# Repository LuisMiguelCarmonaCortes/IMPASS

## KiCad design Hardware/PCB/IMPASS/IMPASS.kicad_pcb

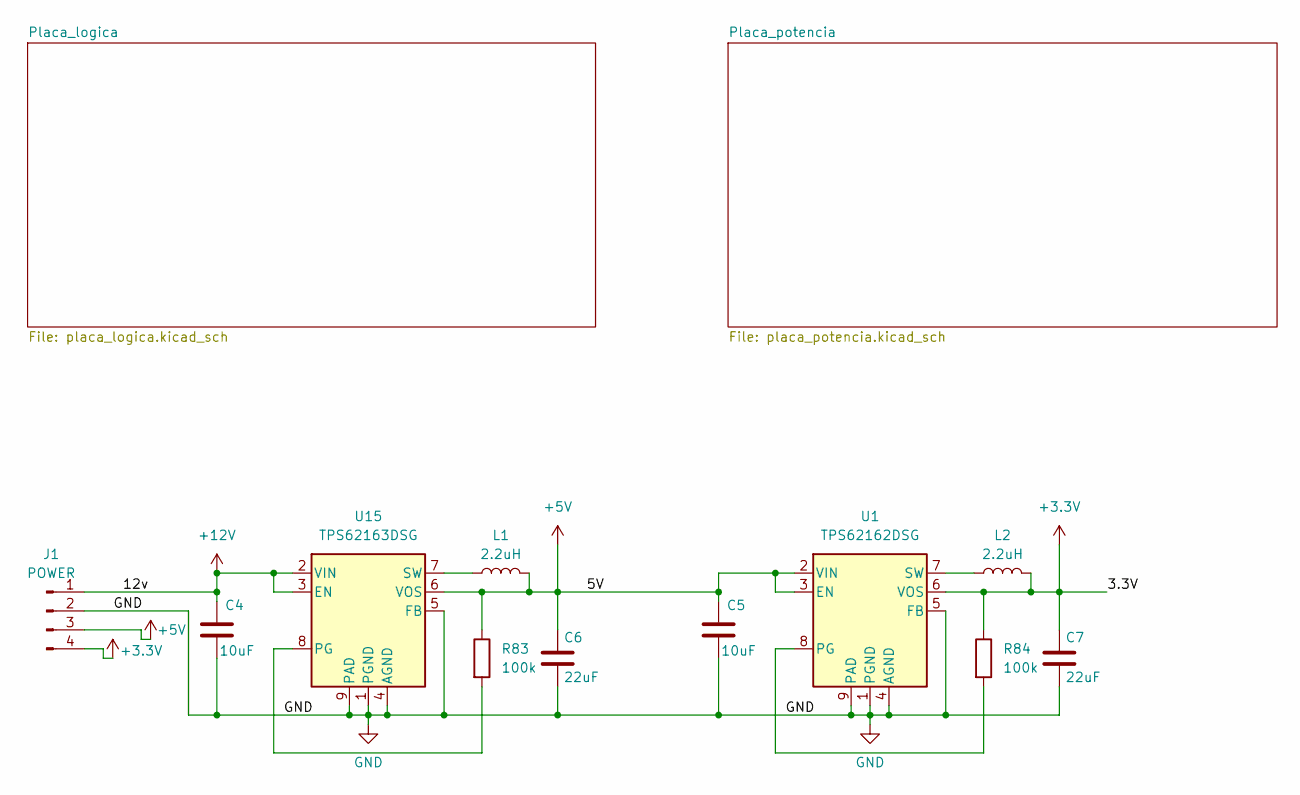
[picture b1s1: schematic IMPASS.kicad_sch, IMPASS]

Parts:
C4, C5: 10uF; C_0805_2012Metric
C6, C7: 22uF; C_0603_1608Metric
J1: POWER; PinHeader_1x04_P2.54mm_Vertical
L1, L2: 2.2uH; L_0603_1608Metric
R83, R84: 100k; R_0603_1608Metric
U1: TPS62162DSG; WSON-8-1EP_2x2mm_P0.5mm_EP0.9x1.6mm_ThermalVias
U15: TPS62163DSG; WSON-8-1EP_2x2mm_P0.5mm_EP0.9x1.6mm_ThermalVias

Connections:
+3.3V: C7.1, J1.4, L2.2, R84.1, U1.6 (VOS); also elsewhere on the board
+5V: C5.1, C6.1, J1.3, L1.2, R83.1, U1.2 (VIN), U1.3 (EN), U15.6 (VOS); also elsewhere on the board
+12V: C4.1, J1.1, U15.2 (VIN), U15.3 (EN); also elsewhere on the board
GND: C4.2, C5.2, C6.2, C7.2, J1.2, U1.1 (PGND), U1.4 (AGND), U1.5 (FB), U1.9 (PAD), U15.1 (PGND), U15.4 (AGND), U15.5 (FB), U15.9 (PAD); also elsewhere on the board
unnamed: R84.2, U1.8 (PG)
unnamed: L2.1, U1.7 (SW)
unnamed: R83.2, U15.8 (PG)
unnamed: L1.1, U15.7 (SW)

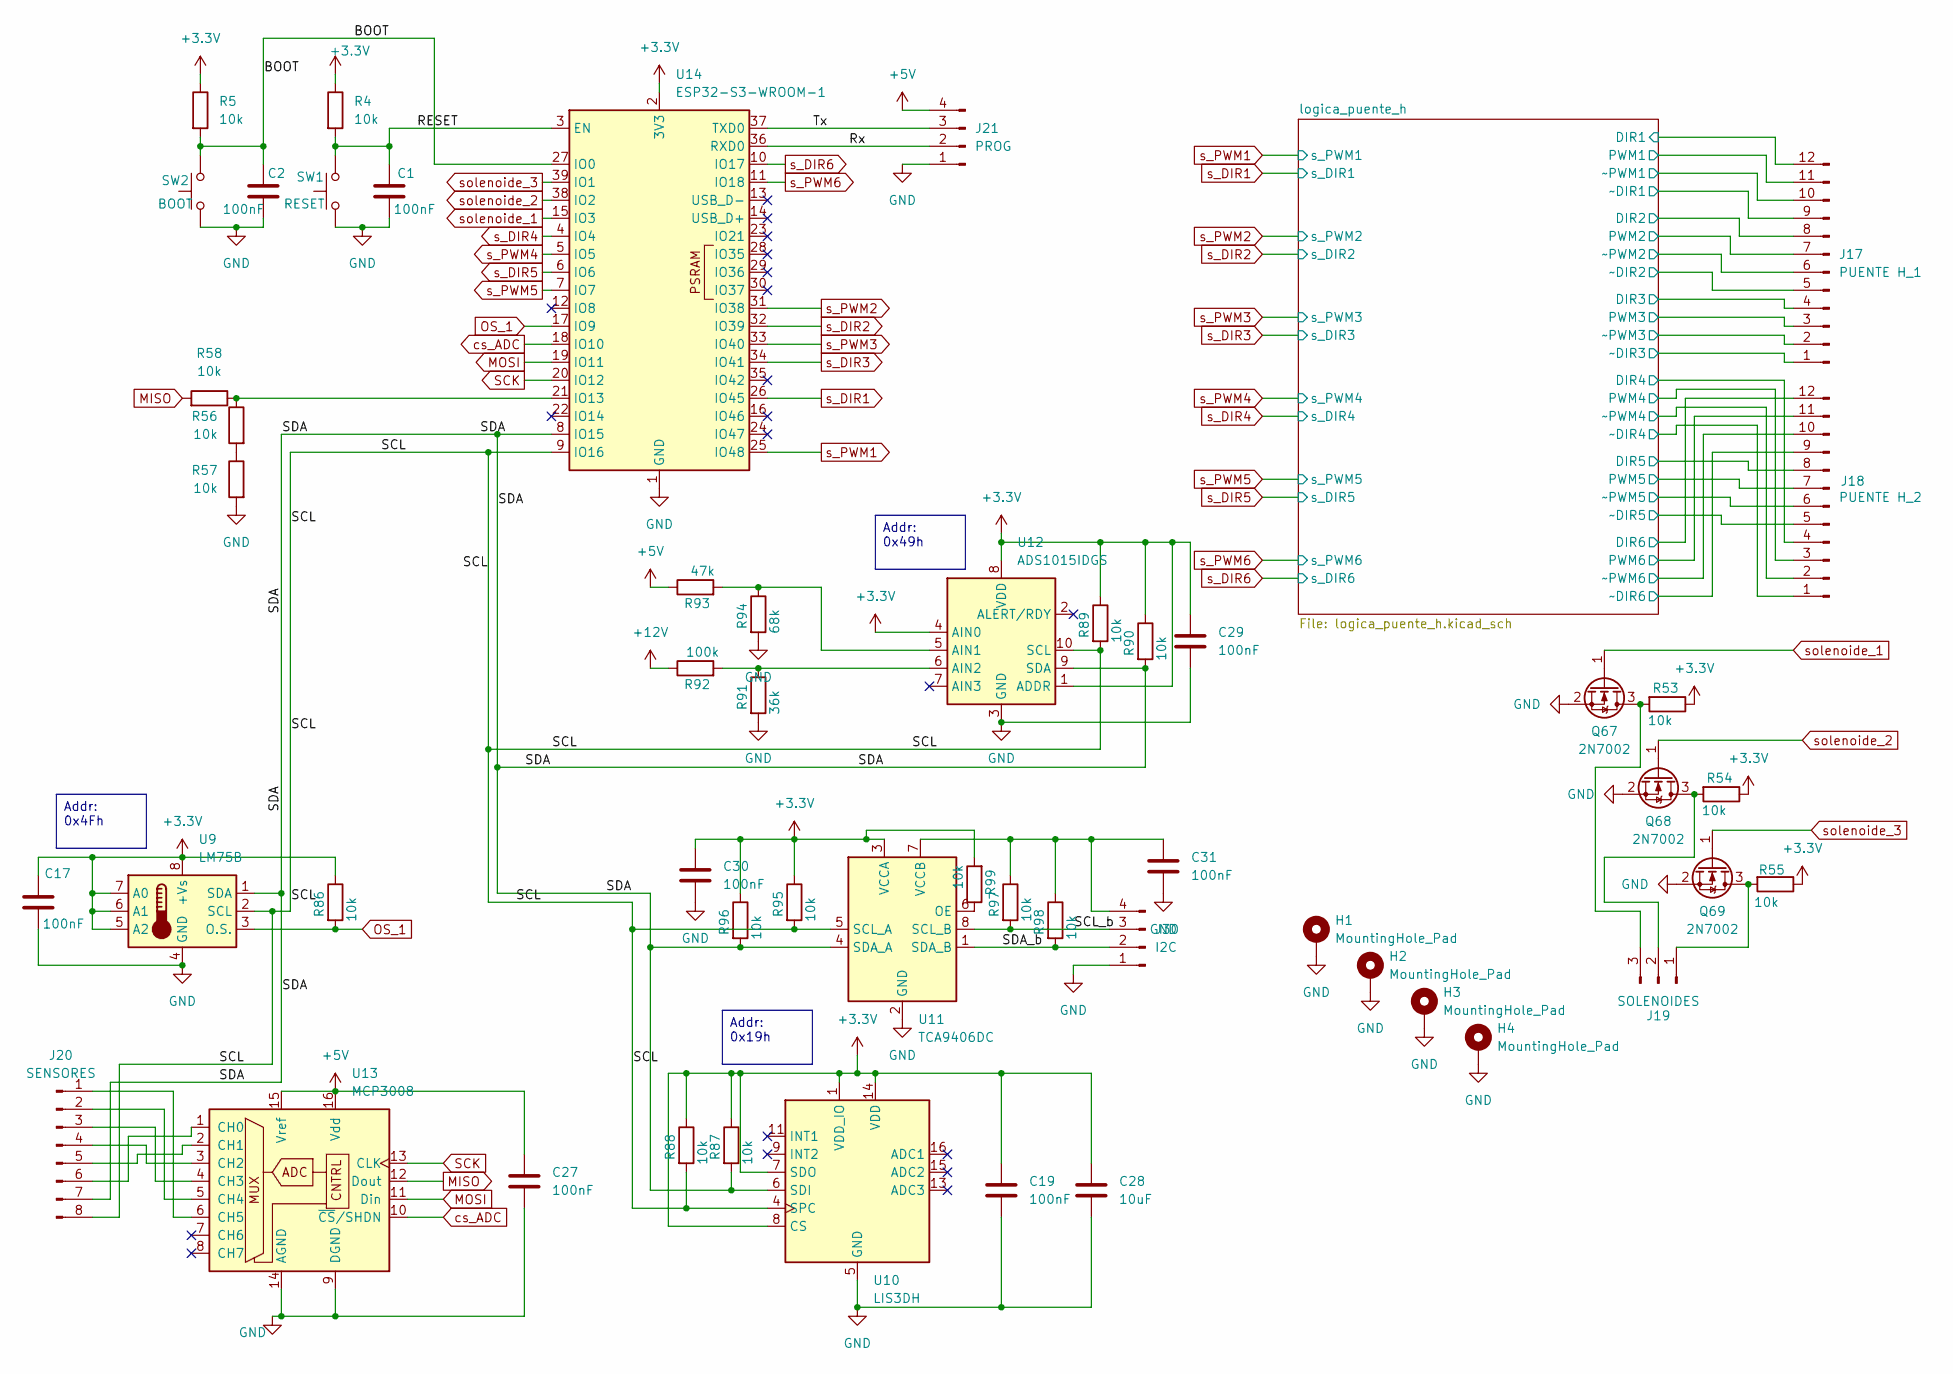
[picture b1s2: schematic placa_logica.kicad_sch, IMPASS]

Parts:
C1, C2, C17, C19, C27, C29, C30, C31: 100nF; C_0603_1608Metric
C28: 10uF; C_0603_1608Metric
H1, H2, H3, H4: MountingHole_Pad; MountingHole_2.2mm_M2_DIN965_Pad
J17: PUENTE H_1; PinHeader_1x12_P2.54mm_Vertical
J18: PUENTE H_2; PinHeader_1x12_P2.54mm_Vertical
J19: SOLENOIDES; PinHeader_1x03_P2.54mm_Vertical
J20: SENSORES; PinHeader_1x08_P2.54mm_Vertical
J21: PROG; PinHeader_1x04_P2.54mm_Horizontal
J30: I2C; PinHeader_1x04_P2.54mm_Horizontal
Q67, Q68, Q69: 2N7002; SOT-23
R4, R5, R53, R54, R55, R56, R57, R58, R86, R87, R88, R89, R90, R95, R96, R97, R98, R99: 10k; R_0603_1608Metric
R91: 36k; R_0603_1608Metric
R92: 100k; R_0603_1608Metric
R93: 47k; R_0603_1608Metric
R94: 68k; R_0603_1608Metric
SW1: RESET; SW_PUSH_6mm_H5mm
SW2: BOOT; SW_PUSH_6mm_H5mm
U9: LM75B; SOIC-8_3.9x4.9mm_P1.27mm
U10: LIS3DH; LGA-16_3x3mm_P0.5mm_LayoutBorder3x5y
U11: TCA9406DC; SSOP-8_2.95x2.8mm_P0.65mm
U12: ADS1015IDGS; TSSOP-10_3x3mm_P0.5mm
U13: MCP3008; SOIC-16_3.9x9.9mm_P1.27mm
U14: ESP32-S3-WROOM-1

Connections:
+3.3V: C17.1, C19.1, C28.1, C29.1, C30.1, R4.1, R5.1, R53.1, R54.1, R55.1, R86.1, R87.1, R88.1, R89.1, R90.1, R95.1, R96.1, R99.2, U9.5 (A2), U9.6 (A1), U9.7 (A0), U9.8 (+Vs), U10.1 (VDD_IO), U10.7 (SDO), U10.8 (CS), U10.14 (VDD), U11.3 (VCCA), U12.1 (ADDR), U12.4 (AIN0), U12.8 (VDD), U14.2 (3V3); also elsewhere on the board
+5V: C27.1, J21.4, R93.1, U13.15 (Vref), U13.16 (Vdd); also elsewhere on the board
+12V: R92.1; also elsewhere on the board
/Placa_logica/BOOT: C2.1, R5.2, SW2.2, U14.27 (IO0)
/Placa_logica/RESET: C1.1, R4.2, SW1.2, U14.3 (EN)
/Placa_logica/Rx: J21.2, U14.36 (RXD0)
/Placa_logica/SCL: J20.8, R88.2, R89.2, R95.2, U9.2 (SCL), U10.4 (SPC), U11.5 (SCL_A), U12.10 (SCL), U14.9 (IO16)
/Placa_logica/SCL_b: J30.3, R97.2, U11.8 (SCL_B)
/Placa_logica/SDA: J20.7, R87.2, R90.2, R96.2, U9.1 (SDA), U10.6 (SDI), U11.4 (SDA_A), U12.9 (SDA), U14.8 (IO15)
/Placa_logica/SDA_b: J30.2, R98.2, U11.1 (SDA_B)
/Placa_logica/Tx: J21.3, U14.37 (TXD0)
/Placa_logica/logica_puente_h/PWM1: J17.11; also elsewhere on the board
/Placa_logica/logica_puente_h/PWM2: J17.7; also elsewhere on the board
/Placa_logica/logica_puente_h/PWM3: J17.3; also elsewhere on the board
/Placa_logica/logica_puente_h/PWM4: J18.3; also elsewhere on the board
/Placa_logica/logica_puente_h/PWM5: J18.7; also elsewhere on the board
/Placa_logica/logica_puente_h/PWM6: J18.11; also elsewhere on the board
/Placa_logica/logica_puente_h/~DIR1: J17.9; also elsewhere on the board
/Placa_logica/logica_puente_h/~DIR2: J17.5; also elsewhere on the board
/Placa_logica/logica_puente_h/~DIR3: J17.1; also elsewhere on the board
/Placa_logica/logica_puente_h/~DIR4: J18.1; also elsewhere on the board
/Placa_logica/logica_puente_h/~DIR5: J18.5; also elsewhere on the board
/Placa_logica/logica_puente_h/~DIR6: J18.9; also elsewhere on the board
/Placa_logica/logica_puente_h/~PWM1: J17.10; also elsewhere on the board
/Placa_logica/logica_puente_h/~PWM2: J17.6; also elsewhere on the board
/Placa_logica/logica_puente_h/~PWM3: J17.2; also elsewhere on the board
/Placa_logica/logica_puente_h/~PWM4: J18.2; also elsewhere on the board
/Placa_logica/logica_puente_h/~PWM5: J18.6; also elsewhere on the board
/Placa_logica/logica_puente_h/~PWM6: J18.10; also elsewhere on the board
GND: C1.2, C2.2, C17.2, C19.2, C27.2, C28.2, C29.2, C30.2, C31.2, H1.1 (1_1), H2.1 (1_1), H3.1 (1_1), H4.1 (1_1), J21.1, J30.1, Q67.2 (S), Q68.2 (S), Q69.2 (S), R57.2, R91.2, R94.2, SW1.1, SW2.1, U9.4 (GND), U10.5 (GND), U10.10 (GND), U10.12 (GND), U11.2 (GND), U12.3 (GND), U13.9 (DGND), U13.14 (AGND), U14.1 (GND), U14.40 (GND), U14.41 (GND); also elsewhere on the board
MISO: R58.2, U13.12 (Dout)
MOSI: U13.11 (Din), U14.19 (IO11)
unnamed: J19.1, Q69.3 (D), R55.2
unnamed: J19.2, Q68.3 (D), R54.2
unnamed: J19.3, Q67.3 (D), R53.2
unnamed: J20.1, U13.6 (CH5)
unnamed: J20.2, U13.5 (CH4)
unnamed: J20.3, U13.4 (CH3)
unnamed: J20.4, U13.3 (CH2)
unnamed: J20.5, U13.2 (CH1)
unnamed: J20.6, U13.1 (CH0)
unnamed: C31.1, J30.4, R97.1, R98.1, U11.7 (VCCB)
unnamed: R56.2, R57.1
unnamed: R99.1, U11.6 (OE)
unnamed: R93.2, R94.1, U12.5 (AIN1)
unnamed: R91.1, R92.2, U12.6 (AIN2)
unnamed: R56.1, R58.1, U14.21 (IO13)
OS_1: R86.2, U9.3 (O.S.), U14.17 (IO9)
SCK: U13.13 (CLK), U14.20 (IO12)
cs_ADC: U13.10 (~CS/SHDN), U14.18 (IO10)
s_DIR1: J17.12, U14.26 (IO45); also elsewhere on the board
s_DIR2: J17.8, U14.32 (IO39); also elsewhere on the board
s_DIR3: J17.4, U14.34 (IO41); also elsewhere on the board
s_DIR4: J18.4, U14.4 (IO4); also elsewhere on the board
s_DIR5: J18.8, U14.6 (IO6); also elsewhere on the board
s_DIR6: J18.12, U14.10 (IO17); also elsewhere on the board
s_PWM1: U14.25 (IO48); also elsewhere on the board
s_PWM2: U14.31 (IO38); also elsewhere on the board
s_PWM3: U14.33 (IO40); also elsewhere on the board
s_PWM4: U14.5 (IO5); also elsewhere on the board
s_PWM5: U14.7 (IO7); also elsewhere on the board
s_PWM6: U14.11 (IO18); also elsewhere on the board
solenoide_1: Q67.1 (G), U14.15 (IO3)
solenoide_2: Q68.1 (G), U14.38 (IO2)
solenoide_3: Q69.1 (G), U14.39 (IO1)

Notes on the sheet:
Addr: 0x4Fh
Addr: 0x19h
Addr: 0x49h

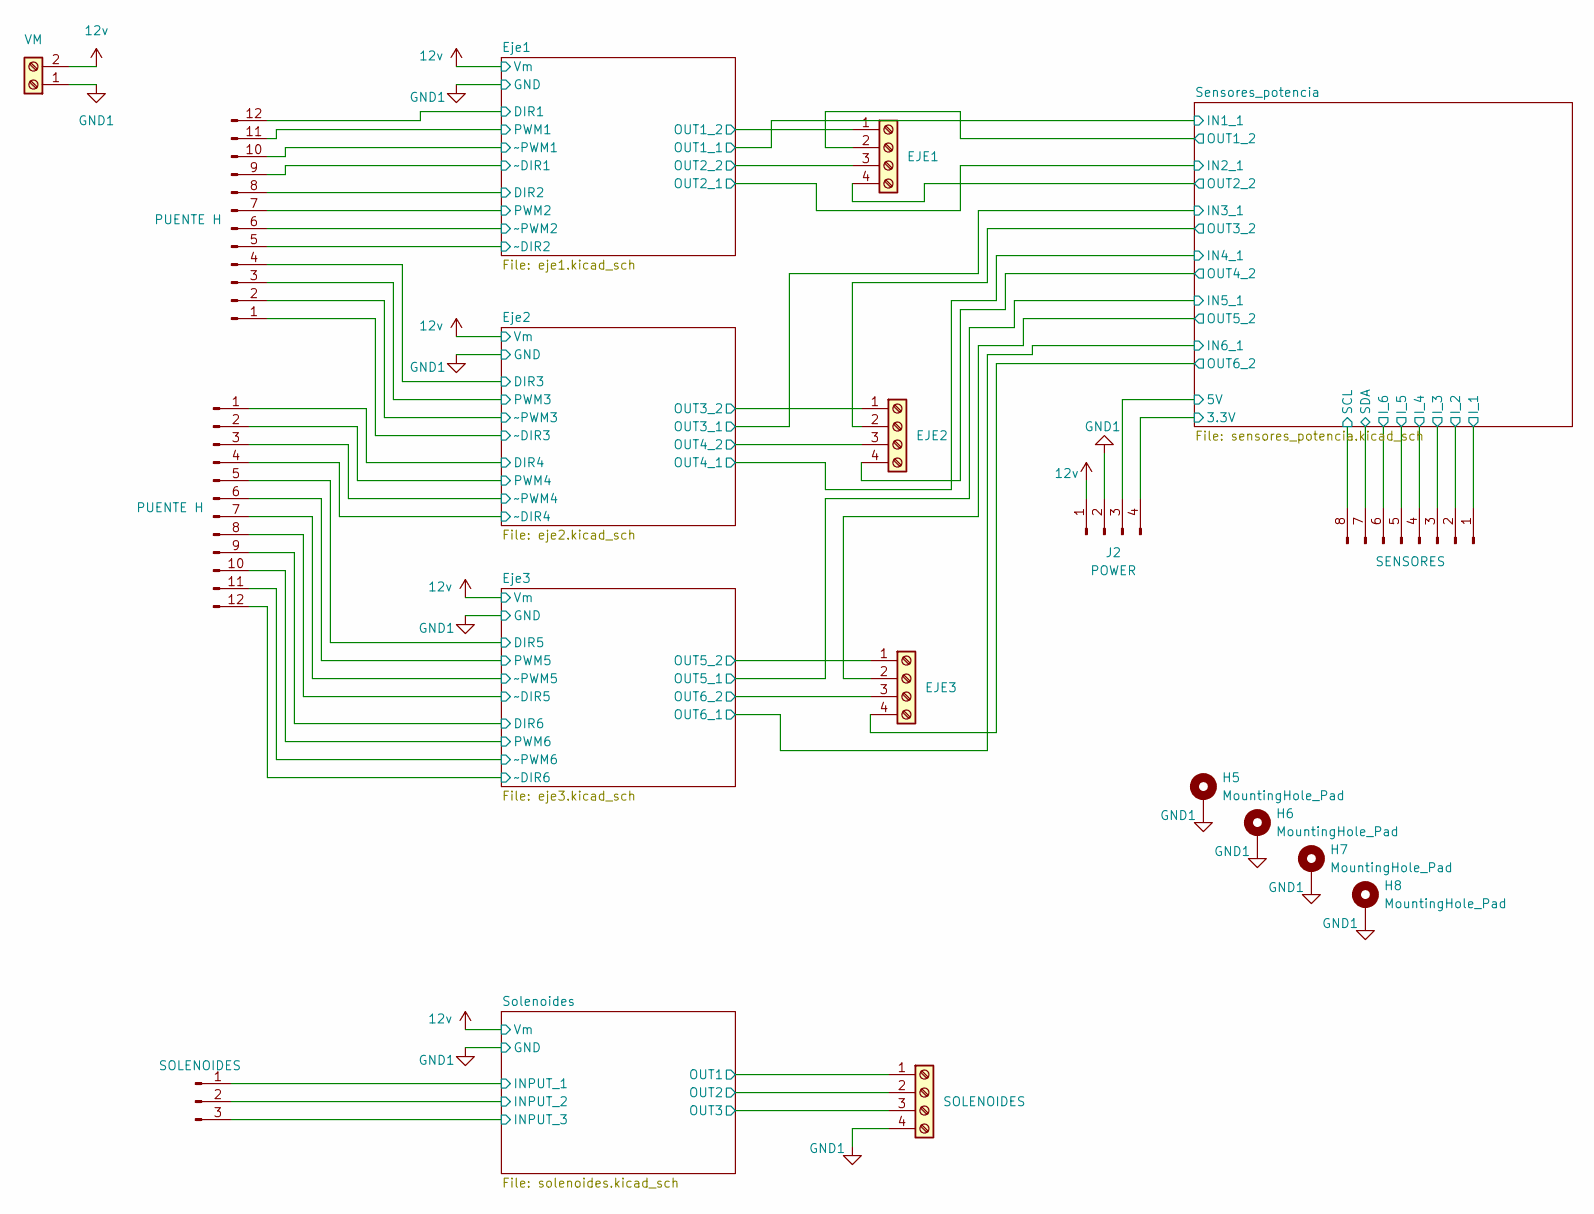
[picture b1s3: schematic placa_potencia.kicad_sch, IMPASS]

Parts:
H5, H6, H7, H8: MountingHole_Pad; MountingHole_2.2mm_M2_DIN965_Pad
J2: POWER; PinHeader_1x04_P2.54mm_Vertical
J11: SOLENOIDES; PinHeader_1x03_P2.54mm_Vertical
J22: VM; TerminalBlock_Phoenix_PT-1,5-2-3.5-H_1x02_P3.50mm_Horizontal
J23: EJE1; TerminalBlock_Phoenix_PT-1,5-4-3.5-H_1x04_P3.50mm_Horizontal
J24: EJE2; TerminalBlock_Phoenix_PT-1,5-4-3.5-H_1x04_P3.50mm_Horizontal
J25: EJE3; TerminalBlock_Phoenix_PT-1,5-4-3.5-H_1x04_P3.50mm_Horizontal
J26: SOLENOIDES; TerminalBlock_Phoenix_PT-1,5-4-3.5-H_1x04_P3.50mm_Horizontal
J27, J28: PUENTE H; PinHeader_1x12_P2.54mm_Vertical
J29: SENSORES; PinHeader_1x08_P2.54mm_Vertical

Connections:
12v: J2.1, J22.2; also elsewhere on the board
/Placa_potencia/Eje1/DIR1: J28.12; also elsewhere on the board
/Placa_potencia/Eje1/DIR2: J28.8; also elsewhere on the board
/Placa_potencia/Eje1/OUT1_2: J23.1; also elsewhere on the board
/Placa_potencia/Eje1/OUT2_2: J23.3; also elsewhere on the board
/Placa_potencia/Eje1/PWM1: J28.11; also elsewhere on the board
/Placa_potencia/Eje1/PWM2: J28.7; also elsewhere on the board
/Placa_potencia/Eje1/~DIR1: J28.9; also elsewhere on the board
/Placa_potencia/Eje1/~DIR2: J28.5; also elsewhere on the board
/Placa_potencia/Eje1/~PWM1: J28.10; also elsewhere on the board
/Placa_potencia/Eje1/~PWM2: J28.6; also elsewhere on the board
/Placa_potencia/Eje2/DIR3: J28.4; also elsewhere on the board
/Placa_potencia/Eje2/DIR4: J27.1; also elsewhere on the board
/Placa_potencia/Eje2/OUT3_2: J24.1; also elsewhere on the board
/Placa_potencia/Eje2/OUT4_2: J24.3; also elsewhere on the board
/Placa_potencia/Eje2/PWM3: J28.3; also elsewhere on the board
/Placa_potencia/Eje2/PWM4: J27.2; also elsewhere on the board
/Placa_potencia/Eje2/~DIR3: J28.1; also elsewhere on the board
/Placa_potencia/Eje2/~DIR4: J27.4; also elsewhere on the board
/Placa_potencia/Eje2/~PWM3: J28.2; also elsewhere on the board
/Placa_potencia/Eje2/~PWM4: J27.3; also elsewhere on the board
/Placa_potencia/Eje3/DIR5: J27.5; also elsewhere on the board
/Placa_potencia/Eje3/DIR6: J27.9; also elsewhere on the board
/Placa_potencia/Eje3/OUT5_2: J25.1; also elsewhere on the board
/Placa_potencia/Eje3/OUT6_2: J25.3; also elsewhere on the board
/Placa_potencia/Eje3/PWM5: J27.6; also elsewhere on the board
/Placa_potencia/Eje3/PWM6: J27.10; also elsewhere on the board
/Placa_potencia/Eje3/~DIR5: J27.8; also elsewhere on the board
/Placa_potencia/Eje3/~DIR6: J27.12; also elsewhere on the board
/Placa_potencia/Eje3/~PWM5: J27.7; also elsewhere on the board
/Placa_potencia/Eje3/~PWM6: J27.11; also elsewhere on the board
/Placa_potencia/Sensores_potencia/3.3V: J2.4; also elsewhere on the board
/Placa_potencia/Sensores_potencia/5V: J2.3; also elsewhere on the board
/Placa_potencia/Sensores_potencia/I_1: J29.1; also elsewhere on the board
/Placa_potencia/Sensores_potencia/I_2: J29.2; also elsewhere on the board
/Placa_potencia/Sensores_potencia/I_3: J29.3; also elsewhere on the board
/Placa_potencia/Sensores_potencia/I_4: J29.4; also elsewhere on the board
/Placa_potencia/Sensores_potencia/I_5: J29.5; also elsewhere on the board
/Placa_potencia/Sensores_potencia/I_6: J29.6; also elsewhere on the board
/Placa_potencia/Sensores_potencia/OUT1_2: J23.2; also elsewhere on the board
/Placa_potencia/Sensores_potencia/OUT2_2: J23.4; also elsewhere on the board
/Placa_potencia/Sensores_potencia/OUT3_2: J24.2; also elsewhere on the board
/Placa_potencia/Sensores_potencia/OUT4_2: J24.4; also elsewhere on the board
/Placa_potencia/Sensores_potencia/OUT5_2: J25.2; also elsewhere on the board
/Placa_potencia/Sensores_potencia/OUT6_2: J25.4; also elsewhere on the board
/Placa_potencia/Sensores_potencia/SCL: J29.8; also elsewhere on the board
/Placa_potencia/Sensores_potencia/SDA: J29.7; also elsewhere on the board
/Placa_potencia/Solenoides/INPUT_1: J11.1; also elsewhere on the board
/Placa_potencia/Solenoides/INPUT_2: J11.2; also elsewhere on the board
/Placa_potencia/Solenoides/INPUT_3: J11.3; also elsewhere on the board
/Placa_potencia/Solenoides/OUT1: J26.1; also elsewhere on the board
/Placa_potencia/Solenoides/OUT2: J26.2; also elsewhere on the board
/Placa_potencia/Solenoides/OUT3: J26.3; also elsewhere on the board
GND1: H5.1 (1_1), H6.1 (1_1), H7.1 (1_1), H8.1 (1_1), J2.2, J22.1, J26.4; also elsewhere on the board

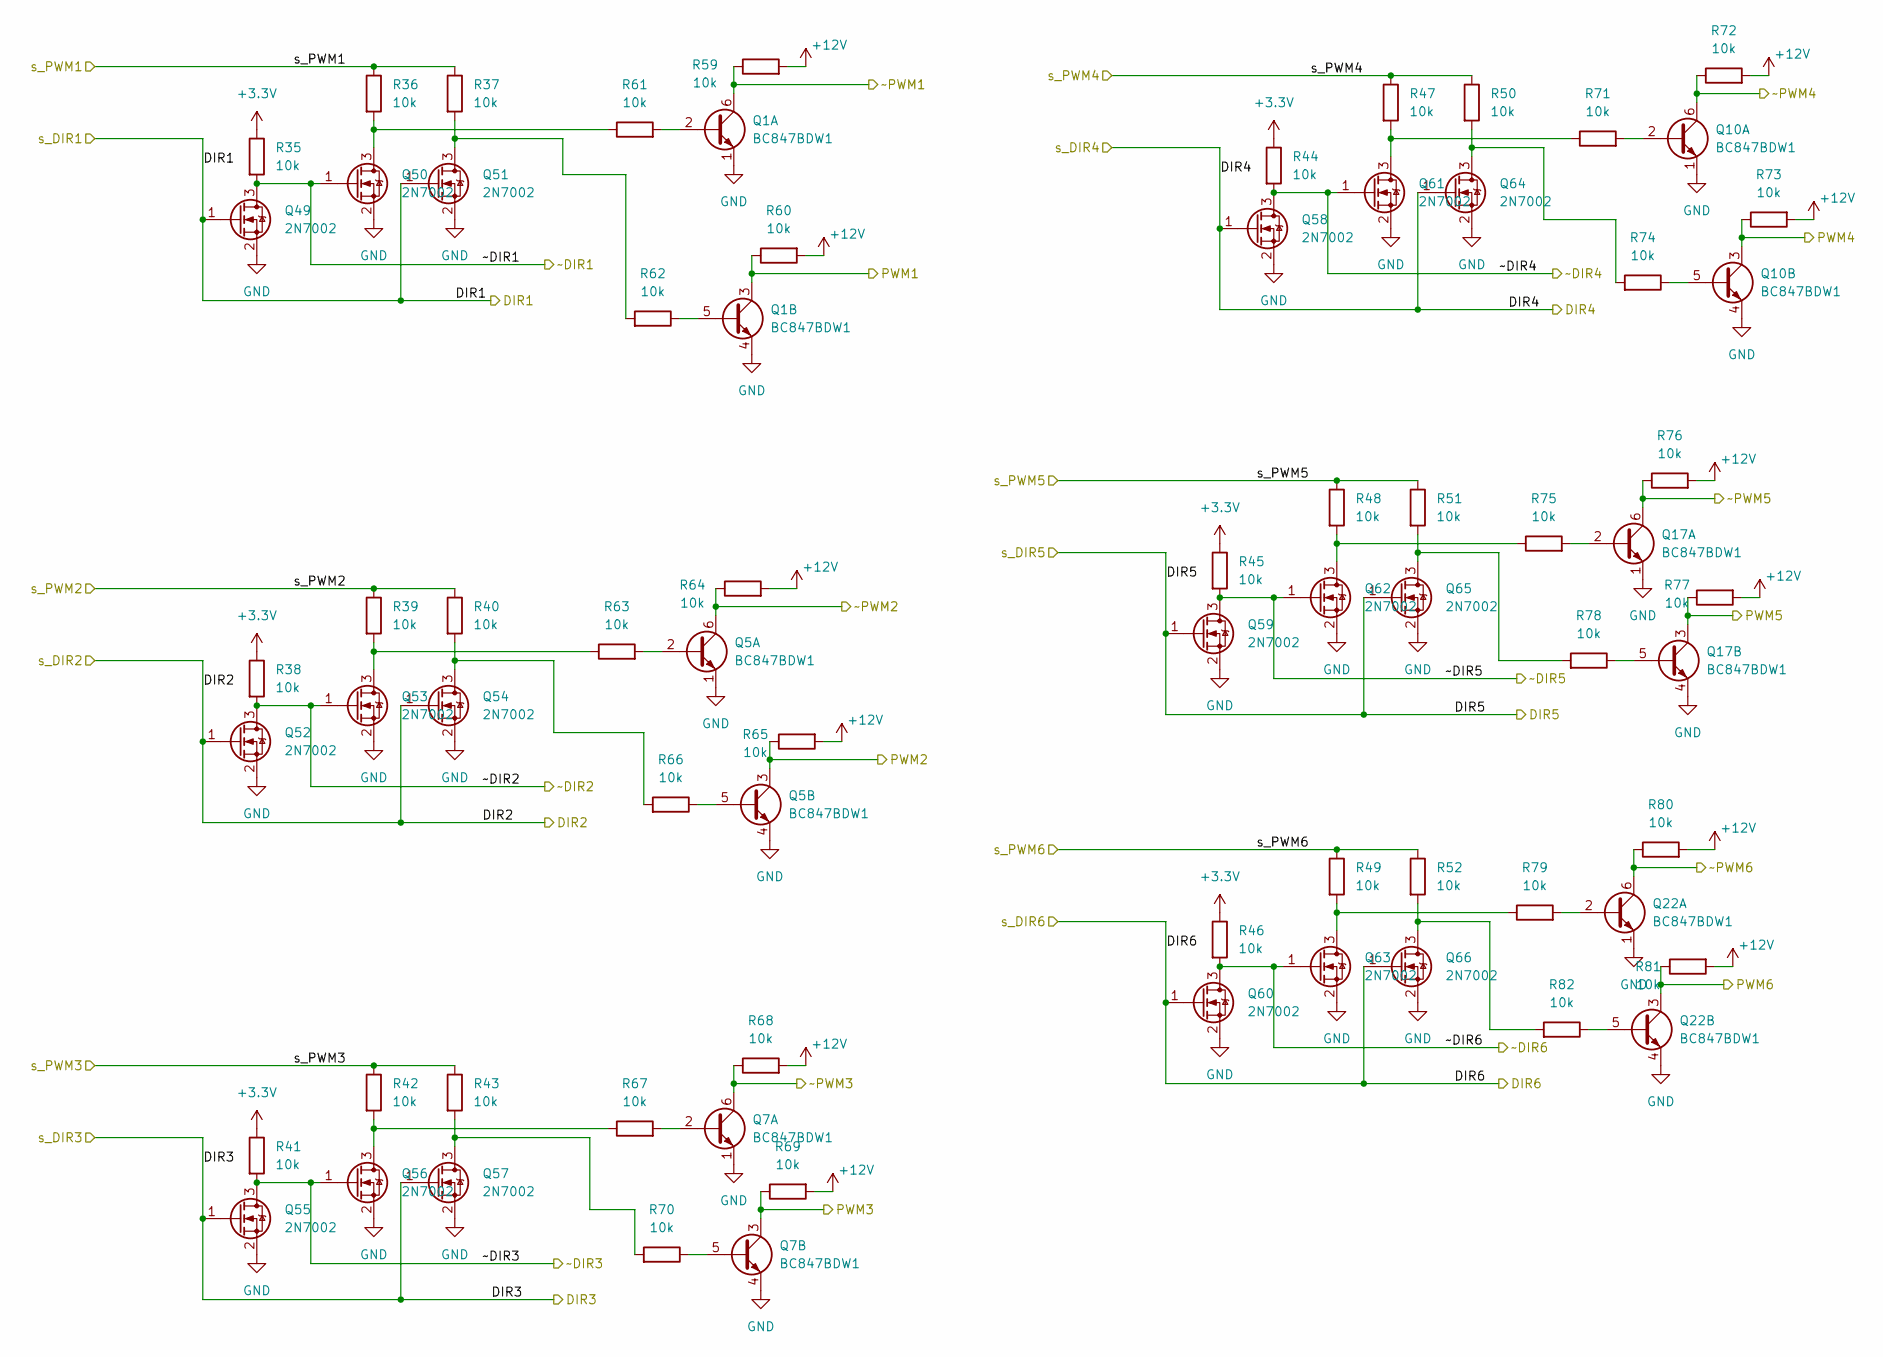
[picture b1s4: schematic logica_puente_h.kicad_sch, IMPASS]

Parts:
Q1, Q5, Q7, Q10, Q17, Q22: BC847BDW1; SOT-363_SC-70-6
Q49, Q50, Q51, Q52, Q53, Q54, Q55, Q56, Q57, Q58, Q59, Q60, Q61, Q62, Q63, Q64, Q65, Q66: 2N7002; SOT-23
R35, R36, R37, R38, R39, R40, R41, R42, R43, R44, R45, R46, R47, R48, R49, R50, R51, R52, R59, R60, R61, R62, R63, R64, R65, R66, R67, R68, R69, R70, R71, R72, R73, R74, R75, R76, R77, R78, R79, R80, R81, R82: 10k; R_0603_1608Metric

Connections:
+3.3V: R35.1, R38.1, R41.1, R44.1, R45.1, R46.1; also elsewhere on the board
+12V: R59.2, R60.2, R64.2, R65.2, R68.2, R69.2, R72.2, R73.2, R76.2, R77.2, R80.2, R81.2; also elsewhere on the board
/Placa_logica/logica_puente_h/PWM1: Q1.3 (C2), R60.1; also elsewhere on the board
/Placa_logica/logica_puente_h/PWM2: Q5.3 (C2), R65.1; also elsewhere on the board
/Placa_logica/logica_puente_h/PWM3: Q7.3 (C2), R69.1; also elsewhere on the board
/Placa_logica/logica_puente_h/PWM4: Q10.3 (C2), R73.1; also elsewhere on the board
/Placa_logica/logica_puente_h/PWM5: Q17.3 (C2), R77.1; also elsewhere on the board
/Placa_logica/logica_puente_h/PWM6: Q22.3 (C2), R81.1; also elsewhere on the board
/Placa_logica/logica_puente_h/~DIR1: Q49.3 (D), Q50.1 (G), R35.2; also elsewhere on the board
/Placa_logica/logica_puente_h/~DIR2: Q52.3 (D), Q53.1 (G), R38.2; also elsewhere on the board
/Placa_logica/logica_puente_h/~DIR3: Q55.3 (D), Q56.1 (G), R41.2; also elsewhere on the board
/Placa_logica/logica_puente_h/~DIR4: Q58.3 (D), Q61.1 (G), R44.2; also elsewhere on the board
/Placa_logica/logica_puente_h/~DIR5: Q59.3 (D), Q62.1 (G), R45.2; also elsewhere on the board
/Placa_logica/logica_puente_h/~DIR6: Q60.3 (D), Q63.1 (G), R46.2; also elsewhere on the board
/Placa_logica/logica_puente_h/~PWM1: Q1.6 (C1), R59.1; also elsewhere on the board
/Placa_logica/logica_puente_h/~PWM2: Q5.6 (C1), R64.1; also elsewhere on the board
/Placa_logica/logica_puente_h/~PWM3: Q7.6 (C1), R68.1; also elsewhere on the board
/Placa_logica/logica_puente_h/~PWM4: Q10.6 (C1), R72.1; also elsewhere on the board
/Placa_logica/logica_puente_h/~PWM5: Q17.6 (C1), R76.1; also elsewhere on the board
/Placa_logica/logica_puente_h/~PWM6: Q22.6 (C1), R80.1; also elsewhere on the board
GND: Q1.1 (E1), Q1.4 (E2), Q5.1 (E1), Q5.4 (E2), Q7.1 (E1), Q7.4 (E2), Q10.1 (E1), Q10.4 (E2), Q17.1 (E1), Q17.4 (E2), Q22.1 (E1), Q22.4 (E2), Q49.2 (S), Q50.2 (S), Q51.2 (S), Q52.2 (S), Q53.2 (S), Q54.2 (S), Q55.2 (S), Q56.2 (S), Q57.2 (S), Q58.2 (S), Q59.2 (S), Q60.2 (S), Q61.2 (S), Q62.2 (S), Q63.2 (S), Q64.2 (S), Q65.2 (S), Q66.2 (S); also elsewhere on the board
unnamed: Q1.2 (B1), R61.2
unnamed: Q1.5 (B2), R62.1
unnamed: Q5.2 (B1), R63.2
unnamed: Q5.5 (B2), R66.1
unnamed: Q7.2 (B1), R67.2
unnamed: Q7.5 (B2), R70.1
unnamed: Q10.2 (B1), R71.2
unnamed: Q10.5 (B2), R74.1
unnamed: Q17.2 (B1), R75.2
unnamed: Q17.5 (B2), R78.1
unnamed: Q22.2 (B1), R79.2
unnamed: Q22.5 (B2), R82.1
unnamed: Q50.3 (D), R36.2, R61.1
unnamed: Q51.3 (D), R37.2, R62.2
unnamed: Q53.3 (D), R39.2, R63.1
unnamed: Q54.3 (D), R40.2, R66.2
unnamed: Q56.3 (D), R42.2, R67.1
unnamed: Q57.3 (D), R43.2, R70.2
unnamed: Q61.3 (D), R47.2, R71.1
unnamed: Q62.3 (D), R48.2, R75.1
unnamed: Q63.3 (D), R49.2, R79.1
unnamed: Q64.3 (D), R50.2, R74.2
unnamed: Q65.3 (D), R51.2, R78.2
unnamed: Q66.3 (D), R52.2, R82.2
s_DIR1: Q49.1 (G), Q51.1 (G); also elsewhere on the board
s_DIR2: Q52.1 (G), Q54.1 (G); also elsewhere on the board
s_DIR3: Q55.1 (G), Q57.1 (G); also elsewhere on the board
s_DIR4: Q58.1 (G), Q64.1 (G); also elsewhere on the board
s_DIR5: Q59.1 (G), Q65.1 (G); also elsewhere on the board
s_DIR6: Q60.1 (G), Q66.1 (G); also elsewhere on the board
s_PWM1: R36.1, R37.1; also elsewhere on the board
s_PWM2: R39.1, R40.1; also elsewhere on the board
s_PWM3: R42.1, R43.1; also elsewhere on the board
s_PWM4: R47.1, R50.1; also elsewhere on the board
s_PWM5: R48.1, R51.1; also elsewhere on the board
s_PWM6: R49.1, R52.1; also elsewhere on the board

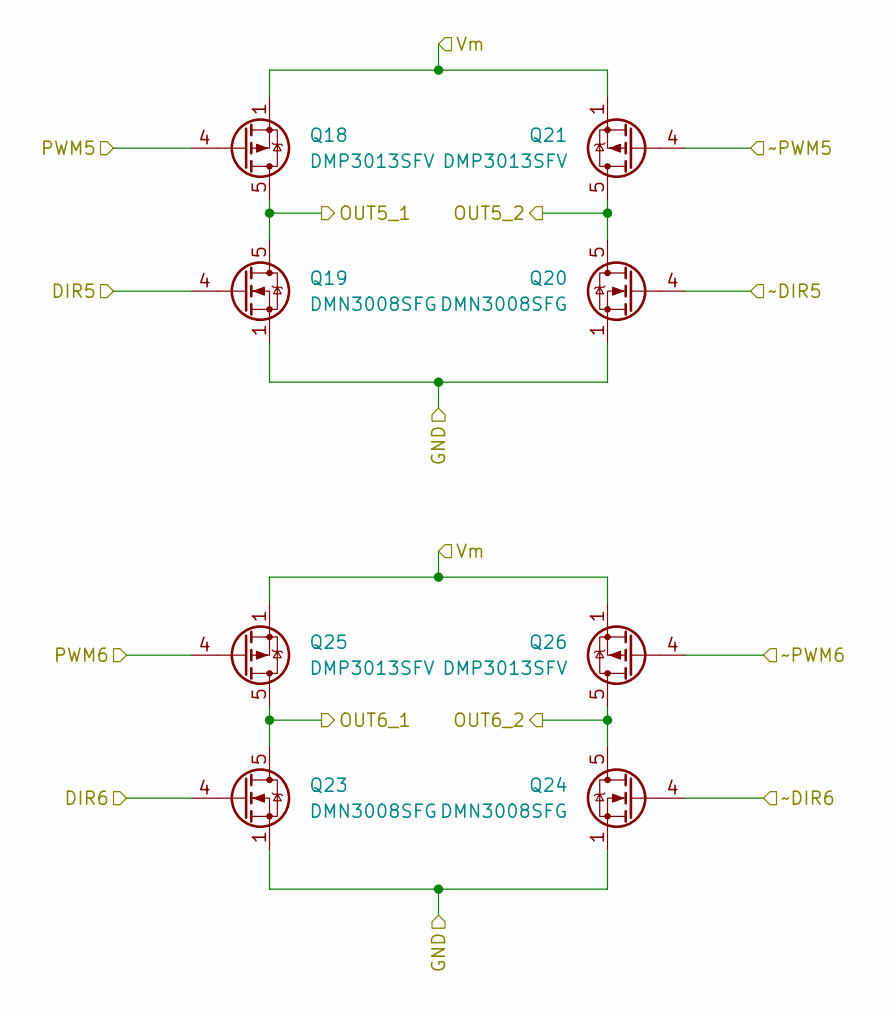
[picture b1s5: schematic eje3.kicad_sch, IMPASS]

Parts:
Q18, Q21, Q25, Q26: DMP3013SFV; Diodes_PowerDI3333-8
Q19, Q20, Q23, Q24: DMN3008SFG; Diodes_PowerDI3333-8

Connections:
12v: Q18.1 (S), Q18.2 (S), Q18.3 (S), Q21.1 (S), Q21.2 (S), Q21.3 (S), Q25.1 (S), Q25.2 (S), Q25.3 (S), Q26.1 (S), Q26.2 (S), Q26.3 (S); also elsewhere on the board
/Placa_potencia/Eje3/DIR5: Q19.4 (G); also elsewhere on the board
/Placa_potencia/Eje3/DIR6: Q23.4 (G); also elsewhere on the board
/Placa_potencia/Eje3/OUT5_1: Q18.5 (D), Q19.5 (D); also elsewhere on the board
/Placa_potencia/Eje3/OUT5_2: Q20.5 (D), Q21.5 (D); also elsewhere on the board
/Placa_potencia/Eje3/OUT6_1: Q23.5 (D), Q25.5 (D); also elsewhere on the board
/Placa_potencia/Eje3/OUT6_2: Q24.5 (D), Q26.5 (D); also elsewhere on the board
/Placa_potencia/Eje3/PWM5: Q18.4 (G); also elsewhere on the board
/Placa_potencia/Eje3/PWM6: Q25.4 (G); also elsewhere on the board
/Placa_potencia/Eje3/~DIR5: Q20.4 (G); also elsewhere on the board
/Placa_potencia/Eje3/~DIR6: Q24.4 (G); also elsewhere on the board
/Placa_potencia/Eje3/~PWM5: Q21.4 (G); also elsewhere on the board
/Placa_potencia/Eje3/~PWM6: Q26.4 (G); also elsewhere on the board
GND1: Q19.1 (S), Q19.2 (S), Q19.3 (S), Q20.1 (S), Q20.2 (S), Q20.3 (S), Q23.1 (S), Q23.2 (S), Q23.3 (S), Q24.1 (S), Q24.2 (S), Q24.3 (S); also elsewhere on the board

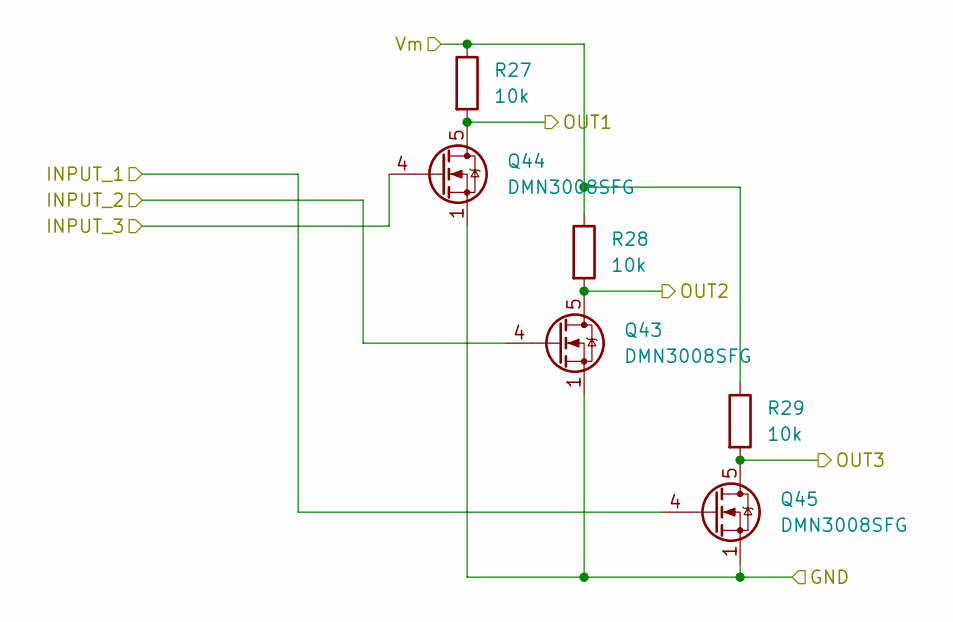
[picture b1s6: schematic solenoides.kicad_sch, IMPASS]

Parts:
Q43, Q44, Q45: DMN3008SFG; Diodes_PowerDI3333-8
R27, R28, R29: 10k; R_0603_1608Metric

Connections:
12v: R27.1, R28.1, R29.1; also elsewhere on the board
/Placa_potencia/Solenoides/INPUT_1: Q45.4 (G); also elsewhere on the board
/Placa_potencia/Solenoides/INPUT_2: Q43.4 (G); also elsewhere on the board
/Placa_potencia/Solenoides/INPUT_3: Q44.4 (G); also elsewhere on the board
/Placa_potencia/Solenoides/OUT1: Q44.5 (D), R27.2; also elsewhere on the board
/Placa_potencia/Solenoides/OUT2: Q43.5 (D), R28.2; also elsewhere on the board
/Placa_potencia/Solenoides/OUT3: Q45.5 (D), R29.2; also elsewhere on the board
GND1: Q43.1 (S), Q43.2 (S), Q43.3 (S), Q44.1 (S), Q44.2 (S), Q44.3 (S), Q45.1 (S), Q45.2 (S), Q45.3 (S); also elsewhere on the board

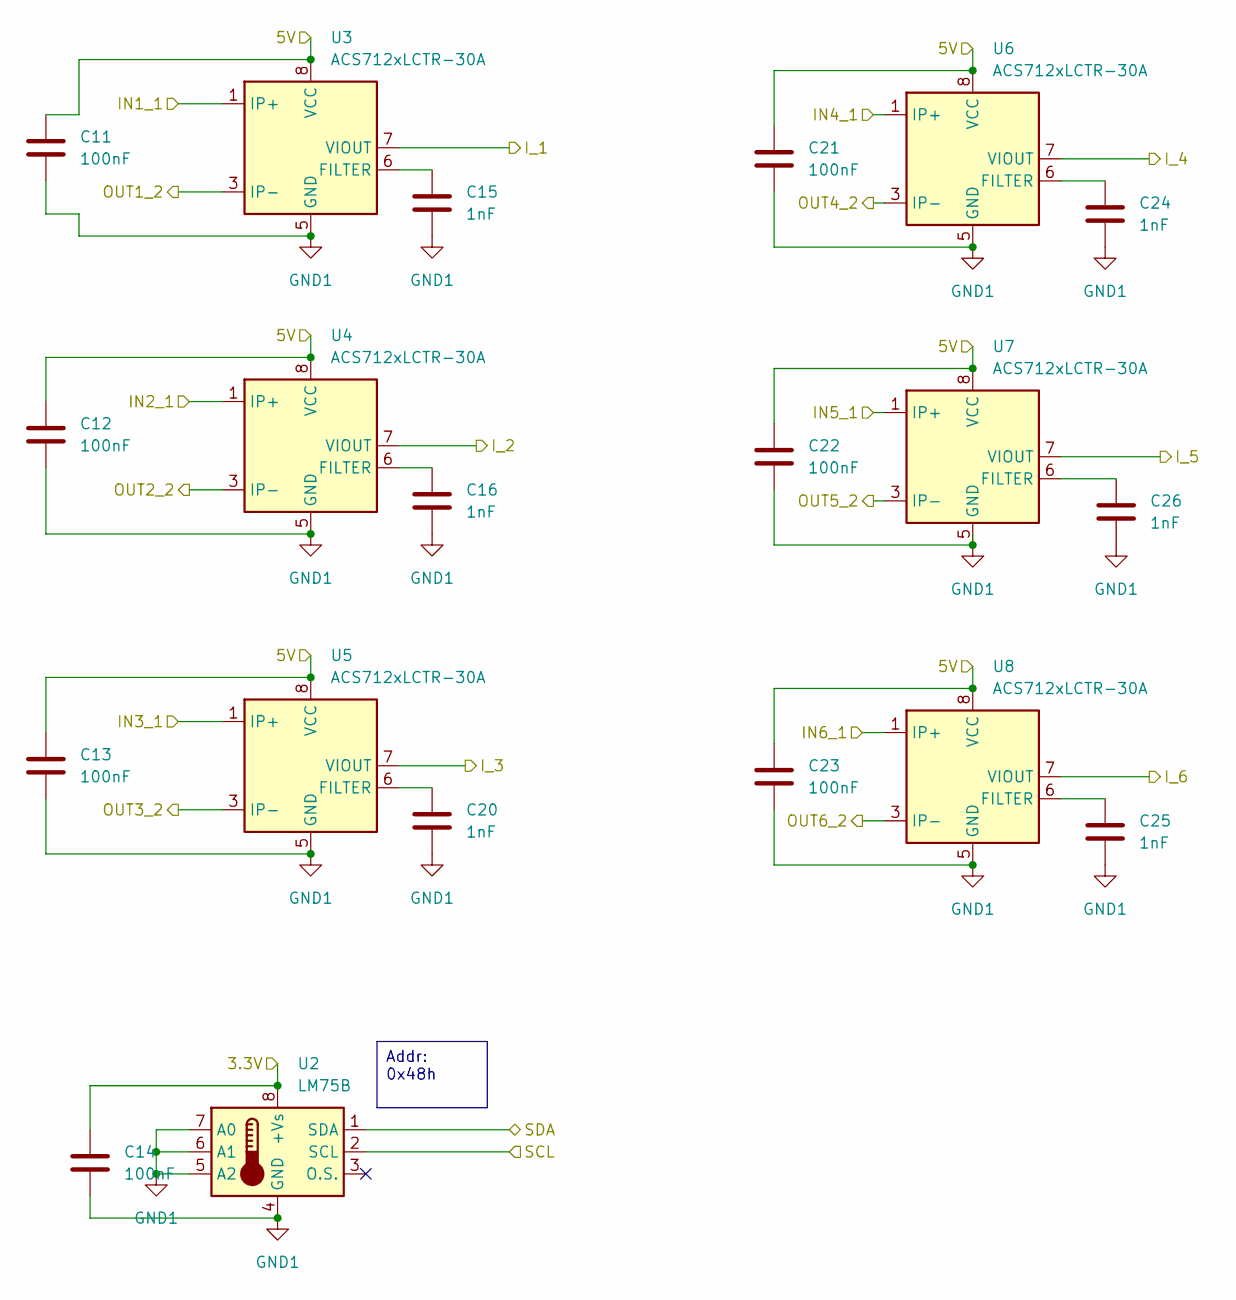
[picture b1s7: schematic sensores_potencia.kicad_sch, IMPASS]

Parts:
C11, C12, C13, C14, C21, C22, C23: 100nF; C_0603_1608Metric
C15, C16, C20, C24, C25, C26: 1nF; C_0603_1608Metric
U2: LM75B; SOIC-8_3.9x4.9mm_P1.27mm
U3, U4, U5, U6, U7, U8: ACS712xLCTR-30A; SOIC-8_3.9x4.9mm_P1.27mm

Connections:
/Placa_potencia/Eje1/OUT1_1: U3.1 (IP+), U3.2 (IP+); also elsewhere on the board
/Placa_potencia/Eje1/OUT2_1: U4.1 (IP+), U4.2 (IP+); also elsewhere on the board
/Placa_potencia/Eje2/OUT3_1: U5.1 (IP+), U5.2 (IP+); also elsewhere on the board
/Placa_potencia/Eje2/OUT4_1: U6.1 (IP+), U6.2 (IP+); also elsewhere on the board
/Placa_potencia/Eje3/OUT5_1: U7.1 (IP+), U7.2 (IP+); also elsewhere on the board
/Placa_potencia/Eje3/OUT6_1: U8.1 (IP+), U8.2 (IP+); also elsewhere on the board
/Placa_potencia/Sensores_potencia/3.3V: C14.1, U2.8 (+Vs); also elsewhere on the board
/Placa_potencia/Sensores_potencia/5V: C11.1, C12.1, C13.1, C21.1, C22.1, C23.1, U3.8 (VCC), U4.8 (VCC), U5.8 (VCC), U6.8 (VCC), U7.8 (VCC), U8.8 (VCC); also elsewhere on the board
/Placa_potencia/Sensores_potencia/I_1: U3.7 (VIOUT); also elsewhere on the board
/Placa_potencia/Sensores_potencia/I_2: U4.7 (VIOUT); also elsewhere on the board
/Placa_potencia/Sensores_potencia/I_3: U5.7 (VIOUT); also elsewhere on the board
/Placa_potencia/Sensores_potencia/I_4: U6.7 (VIOUT); also elsewhere on the board
/Placa_potencia/Sensores_potencia/I_5: U7.7 (VIOUT); also elsewhere on the board
/Placa_potencia/Sensores_potencia/I_6: U8.7 (VIOUT); also elsewhere on the board
/Placa_potencia/Sensores_potencia/OUT1_2: U3.3 (IP-), U3.4 (IP-); also elsewhere on the board
/Placa_potencia/Sensores_potencia/OUT2_2: U4.3 (IP-), U4.4 (IP-); also elsewhere on the board
/Placa_potencia/Sensores_potencia/OUT3_2: U5.3 (IP-), U5.4 (IP-); also elsewhere on the board
/Placa_potencia/Sensores_potencia/OUT4_2: U6.3 (IP-), U6.4 (IP-); also elsewhere on the board
/Placa_potencia/Sensores_potencia/OUT5_2: U7.3 (IP-), U7.4 (IP-); also elsewhere on the board
/Placa_potencia/Sensores_potencia/OUT6_2: U8.3 (IP-), U8.4 (IP-); also elsewhere on the board
/Placa_potencia/Sensores_potencia/SCL: U2.2 (SCL); also elsewhere on the board
/Placa_potencia/Sensores_potencia/SDA: U2.1 (SDA); also elsewhere on the board
GND1: C11.2, C12.2, C13.2, C14.2, C15.2, C16.2, C20.2, C21.2, C22.2, C23.2, C24.2, C25.2, C26.2, U2.4 (GND), U2.5 (A2), U2.6 (A1), U2.7 (A0), U3.5 (GND), U4.5 (GND), U5.5 (GND), U6.5 (GND), U7.5 (GND), U8.5 (GND); also elsewhere on the board
unnamed: C15.1, U3.6 (FILTER)
unnamed: C16.1, U4.6 (FILTER)
unnamed: C20.1, U5.6 (FILTER)
unnamed: C24.1, U6.6 (FILTER)
unnamed: C26.1, U7.6 (FILTER)
unnamed: C25.1, U8.6 (FILTER)

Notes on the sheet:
Addr: 0x48h
